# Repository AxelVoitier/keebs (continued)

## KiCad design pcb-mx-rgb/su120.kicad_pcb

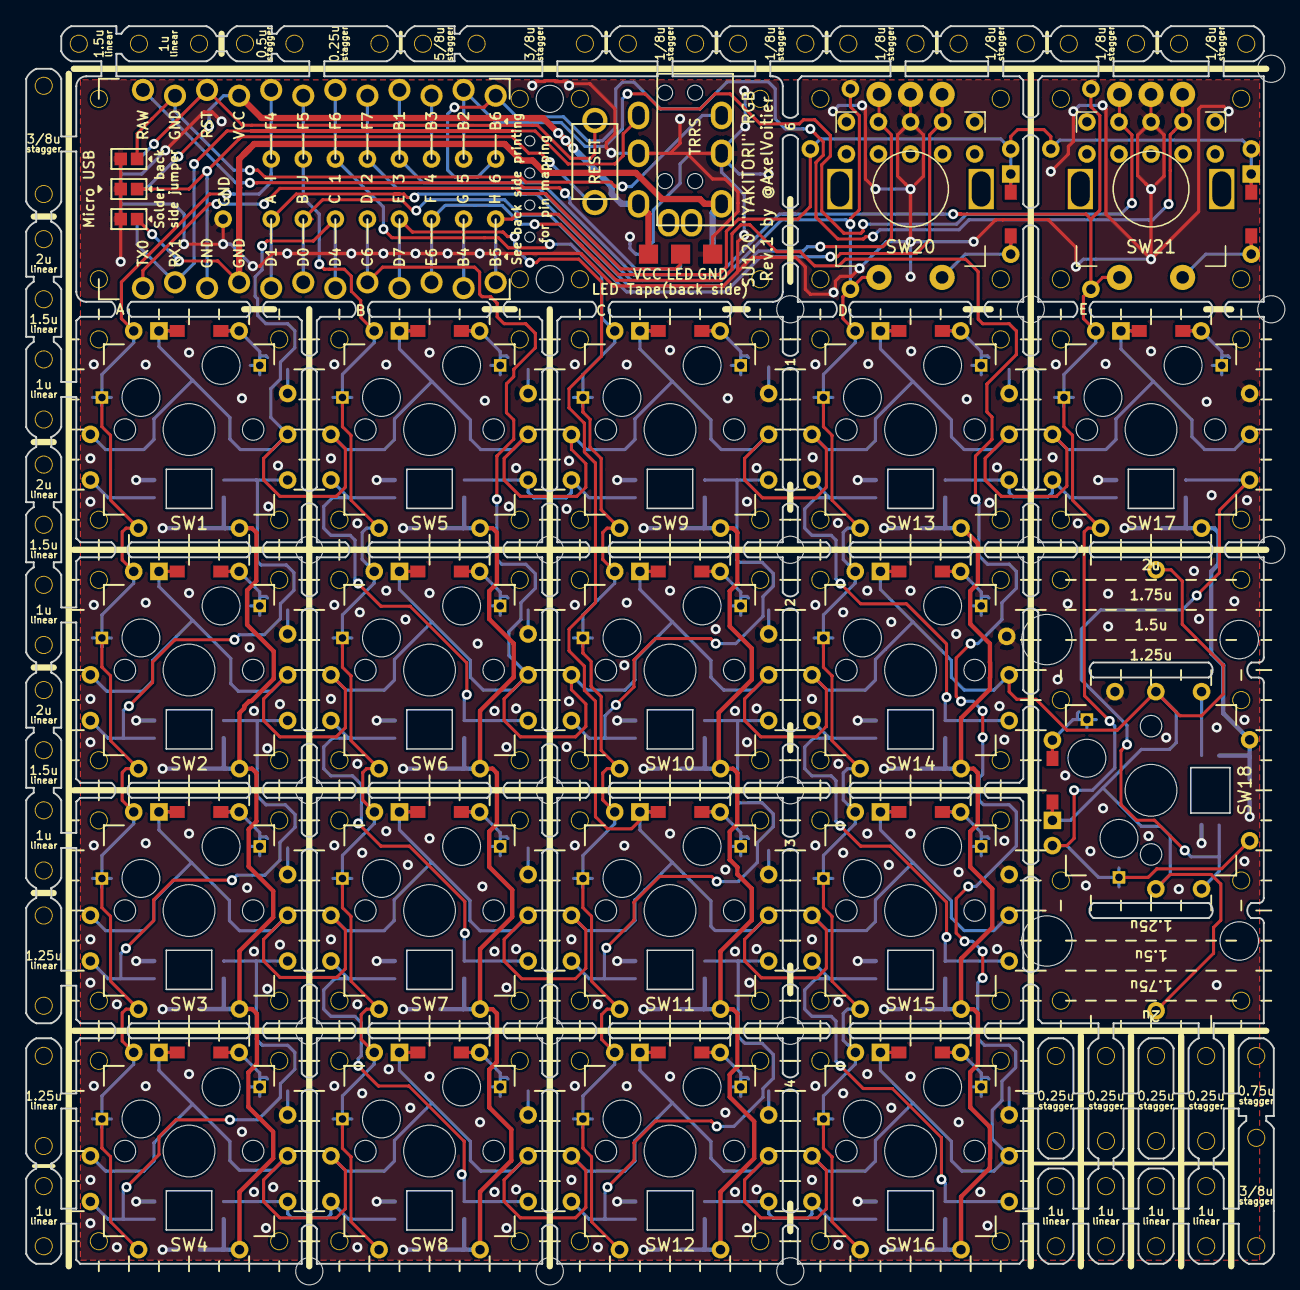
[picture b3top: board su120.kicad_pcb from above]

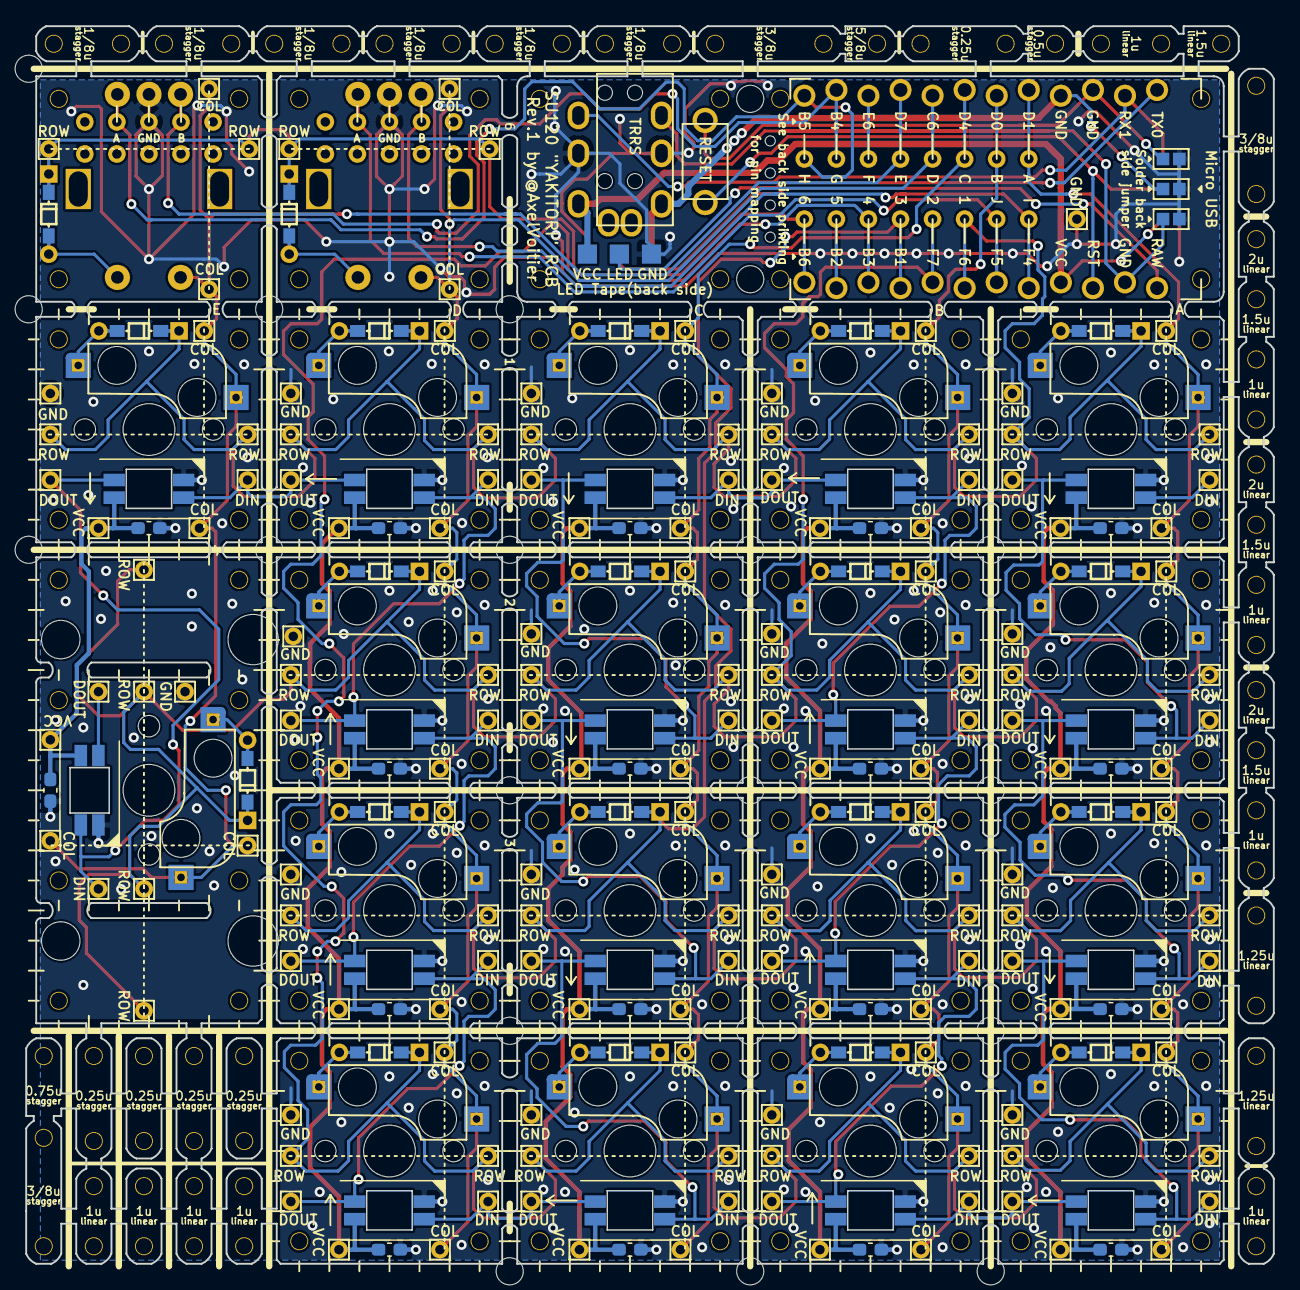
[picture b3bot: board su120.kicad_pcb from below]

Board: 2 copper layers, 98.8 x 98.0 mm, 229 parts (24 on the bottom side), 64 nets.

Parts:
C1, C2, C3, C4, C5, C6, C7, C8, C9, C10, C11, C12, C13, C14, C15, C16, C17, C18: 100n; C_0603_1608Metric_Pad1.08x0.95mm_HandSolder
D1, D2, D3, D4, D5, D6, D7, D8, D9, D10, D11, D12, D13, D14, D15, D16, D17, D18, D19, D20: D; diode_TH_SMD_rev2
H1, H2, H3, H4, H5, H6, H7, H8, H9, H10, H11, H12, H13, H14, H15, H16, H17, H18, H19, H20, H21, H22, H23, H24, H25, H26, H27, H28, H29, H30, H31, H32, H33, H34, H35, H36, H37, H38, H39, H40, H41, H42, H43, H44, H45, H46, H47, H48, H49, H50, H51, H52, H53, H54, H55, H56, H57, H58, H59, H60, H61, H62, H63, H64, H65, H66, H67, H68, H69, H70, H71, H72, H73, H74, H75, H76, H77, H78, H79, H80, H81, H82, H83, H84, H85, H86, H87, H88, H89, H90, H91, H92, H93, H94, H95, H96, H97, H98, H99, H100, H101, H102, H103, H104, H105, H106, H107, H108, H109, H110, H111, H112, H113, H114, H115, H116, H117, H118, H119, H120, H121, H122, H123, H124, H125, H126, H127, H128, H129, H130, H131, H132, H133, H134, H135, H136, H137, H138, H139, H140, H141, H142, H143, H144, H145, H146, H147, H148, H149, H150, H151, H210, H211, H212, H213: MountingHole_Pad; 1pin_conn
J1, J6: MJ-4PP-9
J2, J5: Conn_01x03; StripLED_rev2
J3, J4: Conn_01x08; PinHeader_1x08_P2.54mm_Vertical_rev2
J7, J8: Conn_02x05_Odd_Even; IDC-Header_2x05_P2.54mm_Vertical
JP1, JP2, JP3, JP4, JP5, JP6: SolderJumper_2_Open; SolderJumper-2_P1.3mm_Open_Pad1.0x1.0mm
SW1, SW2, SW3, SW4, SW5, SW6, SW7, SW8, SW9, SW10, SW11, SW12, SW13, SW14, SW15, SW16, SW17, SW18: SW_PUSH_LED; CherryMX_MidHeight_RGB_Hotswap
SW20, SW21: Rotary_Encoder_Switch; RotaryEncoder_Alps_EC11E-Switch_Vertical_H20mm_rev2
SW22: SW_Push; ResetSW
U1: ProMicro; ArduinoProMicro-ZigZag_rev5

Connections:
GND: C1.2, C2.2, C3.2, C4.2, C5.2, C6.2, C7.2, C8.2, C9.2, C10.2, C11.2, C12.2, C13.2, C14.2, C15.2, C16.2, C17.2, C18.2, H52.1, H54.1, H56.1, H57.1, H64.1, H66.1, H68.1, H70.1, H81.1, H83.1, H85.1, H92.1, H94.1, H96.1, H98.1, H109.1, H111.1, H141.1, H143.1, J1.C, J2.3, J5.3, J6.C, J7.6, J8.6, JP1.2, JP2.2, JP3.2, JP4.2, JP5.2, JP6.2, SW1.3, SW2.3, SW3.3, SW4.3, SW5.3, SW6.3, SW7.3, SW8.3, SW9.3, SW10.3, SW11.3, SW12.3, SW13.3, SW14.3, SW15.3, SW16.3, SW17.3, SW18.3, SW20.C, SW21.C
unnamed: D1.2, SW1.6
unnamed: D2.2, SW5.6
unnamed: D3.2, SW9.6
unnamed: D4.2, SW13.6
unnamed: D5.2, SW17.6
unnamed: D6.2, SW2.6
unnamed: D7.2, SW6.6
unnamed: D8.2, SW10.6
unnamed: D9.2, SW14.6
unnamed: D10.2, SW4.6
unnamed: D11.2, SW3.6
unnamed: D12.2, SW7.6
unnamed: D13.2, SW11.6
unnamed: D14.2, SW15.6
unnamed: D15.2, SW8.6
unnamed: D16.2, SW18.6
unnamed: D17.2, SW16.6
unnamed: D18.2, SW20.S2
unnamed: D19.2, SW21.S2
unnamed: D20.2, SW12.6
unnamed: H51.1, SW1.4
unnamed: H53.1, H59.1, SW1.2, SW2.4
unnamed: H55.1, H61.1, SW2.2, SW3.4
unnamed: H65.1, H74.1, SW5.4, SW6.2
unnamed: H67.1, H76.1, SW6.4, SW7.2
unnamed: H72.1, H80.1, SW5.2, SW9.4
unnamed: H78.1, SW18.2
unnamed: H82.1, H87.1, SW9.2, SW10.4
unnamed: H84.1, H89.1, SW10.2, SW11.4
unnamed: H100.1, H108.1, SW13.2, SW17.4
unnamed: H93.1, H102.1, SW13.4, SW14.2
unnamed: H95.1, H104.1, SW14.4, SW15.2
unnamed: H97.1, H106.1, SW15.4, SW16.2
unnamed: H63.1, H110.1, SW3.2, SW4.4
unnamed: H112.1, H147.1, SW4.2, SW8.4
unnamed: H91.1, H142.1, SW11.2, SW12.4
unnamed: H71.1, H145.1, SW17.2, SW18.4
unnamed: H69.1, H149.1, SW7.4, SW8.2
unnamed: H99.1, H151.1, SW12.2, SW16.4
VCC: C1.1, C2.1, C3.1, C4.1, C5.1, C6.1, C7.1, C8.1, C9.1, C10.1, C11.1, C12.1, C13.1, C14.1, C15.1, C16.1, C17.1, C18.1, H58.1, H60.1, H62.1, H73.1, H75.1, H77.1, H79.1, H86.1, H88.1, H90.1, H101.1, H103.1, H105.1, H107.1, H144.1, H146.1, H148.1, H150.1, J1.D, J2.1, JP6.1, SW1.1, SW2.1, SW3.1, SW4.1, SW5.1, SW6.1, SW7.1, SW8.1, SW9.1, SW10.1, SW11.1, SW12.1, SW13.1, SW14.1, SW15.1, SW16.1, SW17.1, SW18.1, U1.21
X1: H1.1, H6.1, H21.1, H25.1, H26.1, H30.1, H113.1, H118.1, J4.1, SW1.5, SW2.5, SW3.5, SW4.5, U1.5
X2: H2.1, H7.1, H22.1, H27.1, H114.1, H117.1, H119.1, H122.1, J4.2, SW5.5, SW6.5, SW7.5, SW8.5, U1.6
X3: H3.1, H8.1, H23.1, H28.1, H115.1, H120.1, H210.1, H211.1, J4.3, SW9.5, SW10.5, SW11.5, SW12.5, U1.7
X4: H4.1, H9.1, H24.1, H29.1, H42.1, H44.1, H116.1, H121.1, H133.1, H135.1, J4.4, SW13.5, SW14.5, SW15.5, SW16.5, SW20.S1, U1.8
X5: H5.1, H10.1, H41.1, H43.1, H134.1, H136.1, J4.5, SW17.5, SW18.5, SW21.S1, U1.9
X6: J4.6, U1.10
X7: J4.7, J8.4, SW21.B, U1.11
X8: J4.8, J8.8, SW21.A, U1.12
X9: J3.1, J7.4, SW20.B, U1.20
X10: J3.2, J7.8, SW20.A, U1.19
Y1: D1.1, D2.1, D3.1, D4.1, D5.1, H11.1, H12.1, H13.1, H14.1, H15.1, H16.1, H17.1, H18.1, H19.1, H20.1, J3.3, U1.18
Y2: D6.1, D7.1, D8.1, D9.1, D16.1, H31.1, H32.1, H33.1, H34.1, H35.1, H36.1, H37.1, H38.1, H45.1, H46.1, H49.1, H50.1, J3.4, U1.17
Y3: D11.1, D12.1, D13.1, D14.1, H123.1, H124.1, H125.1, H126.1, H127.1, H128.1, H129.1, H130.1, J3.5, U1.16
Y4: D10.1, D15.1, D17.1, D20.1, H39.1, H40.1, H47.1, H48.1, H131.1, H132.1, H212.1, H213.1, J3.6, U1.15
Y5: J3.7, U1.14
Y6: D18.1, D19.1, H137.1, H138.1, H139.1, H140.1, J3.8, U1.13
data: J1.B, JP1.1, U1.2
dummyVCC: J5.1, J6.D, JP5.1, U1.4
dummydata: J6.B, JP2.1, U1.23
dummyled: J5.2, U1.24
led: J2.2, U1.1
reset1: JP4.1, SW22.1, U1.22
reset2: JP3.1, SW22.2, U1.3

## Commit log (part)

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2021-10-07 Work In Progress
    - Duplicated original su120
    - Forked the switch footprint to remove choc socket and add RGB chip
    - Started converting columns 1 and 2 to the new footprint
    - Started cleaning the schematic for these columns
    - Added solder points for relaying DIN, DOUT, VCC and GND for the RGB chips in between boards
    - Attempt at new routing strategy in column 1 row 2
2021-10-11 Adding initial top plate for Kyfle.
    Kyfle is a mix of Kyria layout with an extra row, using some Sofle design files, and using a modified (for RGB) su120 bit boards as actual PCB
2021-10-12 Importing PCB design from SU120 branch (was already modified to fit RGB on the branch)
2021-10-12 Working on solutions to hold the main PCB.
    Also cleaned a bit the layers by separating physical dimensions (CrtYrd), functional wiring (Fab) and other construction lines (User).
    Completed the wiring template.
2021-10-15 Settled on a solution to fix the PCB
    It will be hold by the bottom plate only.
2021-10-15 Fixuturing solution for the pro micro board
2021-10-18 Adding 3D model for cherry mx (from Acheron libs), adding generating pretty pictures with it
2021-10-21 Redid some footprints
    - For the pro-micro socketed with rivets, it is now reversible
    - The connector for OLED screen has also been converted to a rivetted version
    - The footprint of the TRRS connector has been corrected according to part datasheet
    - The silkscreen indicating the cut line in between bit boards is now done in some slots footprints
2021-10-25 Massive redesign
    - Realised the design was not reversible. Only solution was to mirror the two diagonal holes of each bit. But one of them was coliding with hotswap socket footprint. Until...
    - I also realised that having the holes at these Y positions made the screw coming on top collide with the bottom of the switch housing...
    - So switched to having two holes right in between each bit (vertically).
    - Then I realised cheap pcb houses can have quite some limitations when it comes to exotic uses of slots. In particular, for jlcpcb:
    * They prefer tabs to be >= 4mm wide
    * They prefer at least 3mm of PCB next to a slot (ie. avoid slim inter-slots parts)
2021-10-28 Plates outlines finished
    Redefined the various outlines of the plates based on the new constrains.
    For the top dimension, I took the largest middle-finger stagerring I could find (Elephant42, at +9.5mm) and rounded it to 10mm max amplitude in the middle finger rail, and used that as reference for 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
    And defined the position of the rest from that.
    Top left M% hole might need to be reviewed.
2021-10-30 Resized M2 slots and holes to 2mm instead of 2.2mm
    After receiving M2 hardware, I noticed 2mm opening would provide a tighter and less wobbly fit than the typical M2 clearance of 2.2mm.
    Also, finished the silkscreen of bottom plate, as well as M2 holes for encoders in top plate.
    At this point, both top and bottom plate could be considered finished.
2021-11-01 It is never done. Adding plethora of plate variants.
    - Variant of the default top plate with less routing involved
    - Variant of a top plate allowing to slide the switches around
    - Variant of that last top plate with less routing involved
    Also moving few minor things here and there.
2021-11-03 Plates: Received M2 and M5 hardware. It's bigger than specified...
    - M5 screw head is ~9.5 instead of 8.7. Was colliding in the top left
    corner with M2 screw for pro micro board. So I shifted up pro micro
    board 0.3mm.
    - M2 screw head is also larger than expected (3.8 instead of 3.2). But
    it is mostly fine as I was designing with 4-4.2mm clearance. Only
    exception was for screws supporting the middle bottom section of top
2021-11-03 Adding footprint for 5-way switch (panasonic and also compatible Alexpress noname one)
    Not used on PCB yet as I haven't found a suitable position
2021-11-04 Tentative routing of the 5-way switch
    Not yet integrated in the main board itself.
2021-11-06 PCB: Adding mouse bites to break away tabs
    And increasing tabs width from 4mm to 5mm.
2021-11-08 Adding Pimonori trackball footprint (for reference)
2021-11-08 Adds mouse bites to top plate with rails
2021-11-11 Massive reorganisation, renaming, and licensing
    Kyfle is now called Lergo
2021-11-11 Pimoroni spelling is hard :D
2021-11-13 Integrating Pimoroni trackball in all top plates.
2021-11-15 Lergo V1.A, ready for first prototype run
2021-11-15 Remove outdated images
2021-11-17 Following modifications for aluminum PCBs, FR4 and Alu variants are now available
2021-11-17 Adding illustrations
2021-11-29 Create basic README.md for now
2023-09-27 Handy: Adding KLE generated output, and first throw at layout
    Layout is a WIP, as it is just imported from my current Lergo setup, but not fully adapted yet.
2023-09-28 Handy: Adapt left nav cluster to use Page up/down, home/end
2023-09-29 Handy: Splitting ergogen config file into few smaller and less confusing files, thanks to a new merge helper tool in keebs.py
2023-09-30 Handy: Many changes to the keymap. Also enhanced the config "language" for it.
2023-10-01 Scripts: Supports setting a custom name in KLE output
2023-10-01 Scripts: Integrate ergogen as a Docker container
    Streamlines the workflow as the generation of points.yaml and units.yaml is no longer manual.
    Ie. using the Makefile, you can now go from just the ergogen config overlays up to the final results (currently mostly KLE output) in one command.
2023-10-03 Bunch of enhancements
    - Now generated coordinates are automatically aligned to top-left corner, with positive Y going down (inverse of ergogen), as this fits most tools. KLE or QMK offsets are no longer needed.
    - Keymap entries are now called legend instead of value.
    - In QMK info.json generation, we now support deleting pre-exsiting entries (that's to purge old fields, or some bogus ones from qmk new-keyboard template).
    - QMK keymap.json generation completed with support for tranparent keycodes, and on-hold layer change (ie. "LT"). It is smart enought to take care of all the little details around using LT correctly.
    AND vvvvvv
    - We can auto generate layout in .c/.h files!!!!!!
2023-10-08 Firmware compilation imporvements
    - Deal with the new way of QMK handling keyboard, keymap and userland.
    - Allows to set configs in keymap.json.
    - Separate info.json from keymap.json generation.
    - When generating info.json, if the keyboard folder does not exist, we use "qmk import-keybord" with the json file to create the keyboard.
    - Add support for various quantum keycodes (bootloader reset, dymanic tapping term, auto shift).
2023-12-30 Adding option to KLE generation to ignore a key or layer
2023-12-31 Handy: Updating readme and images
2024-01-05 Handy: Starting to streamline KiCad generated parts
    Here is implemented the PCB outline footprint generation.
    As a side effect, we also ensure that fp-lib-table KiCad project file includes an Ergogen.pretty footprint library.
2024-01-05 KiCad: Supporting footprints in PCB
2024-01-05 KiCad: Easier API to parse/export
2024-01-06 Kicad, footprints: Supports fp_circle, fp_poly, pad, and model token
    Test with a fairly complex footprint.
    Lotssss of underlaying modifications to make it work.
2024-01-06 Kicad: Significant reduction in verbosity when declaring fields
2024-01-08 Handy: Do not outline mirrored keys
2024-01-14 Handy: Proper case implementation
    Since there is now "preprocessin" capabilities added to ergogen by keebs.py script, it can now calculate precisely some of the difficult points (usually corners) that are defined by intersection and/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
    Tenting holes have been added as well, with an option for the "inner" top tenting screw being either near the middle (to be parallel to the right edge) or all the way to the left (vertically aligned 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
    Also cleaned up a bit all the outlines, added premises of components, starting with promicro, oled screen and te
2024-01-14 Handy: Minor fixes here and there
2024-01-15 KiCad, tests: Fixes tests not passing because of kicad inconsistencies
2024-01-15 Kicad: Fixes for footprint having desr and tags
2024-01-15 Handy: Finally generating a proper outline
2024-01-28 KiCad: Implementing a current parsing context stack
    It can be used by token classes to "specify" some of their behaviour during parsing.
    It should finally be the foundation of a fix for the various KiCad tokens that have the same name but not the same format... (eg. layer).
2024-01-28 KiCad: Adding more flexible newlines control
2024-01-31 Kicad: Nails further issues with angles...
    Despite the special casing done in _angle_normalizer for fp_text and pad, there was still some unnecessary modifications of, eg. 355 to -5.
    This was due to the way footprint are updated: for every item in the model footprint (which usually is built with a 0 degree reference), a new item with angle applied (the one of each particular ref 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
    Issue was that this new item used for comparison to the old one was ha
2024-01-31 KiCad: Fixes bug introduced by one speed optimisation
    In case of loading different kicad_pcb files of different versions within the same instance of a script, some versioned token of the wrong version were weirdly used. But if parsing each file independ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
    Turns out, the method doing the resolution of versioned token was cached in such a way that if later it was used in the context of a different version, then it was using the cached result from the fi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
    Taking the version context out of that method, and instead passing the current version as an argument to it fixes the issue.
2024-02-04 Kicad: Reorganise token classes declarations such that we can use attrs.resolve_types directly in Token.__init_subclass__.
2024-02-24 Linting issues
2026-01-22 Framework, OKM: Adding images
2026-01-22 FW OKM: Reduce aperture to 16.6 mm (was 16.75)
2026-01-24 FW: First throw at Handywork-min layout, a 5x3 adapted to a Framework 16
2026-01-24 HandyWork: Big update with 3 main layouts and 4 more variants
2026-01-25 HandyWork: Keymap and documentation for all 8 proposed layouts
2026-01-25 HandyWork: Adding description of the main properties
2026-02-16 Update on the Framework footprints
2026-02-23 Framework, A1 board footprint: Correction of bottom courtyard
2026-03-01 Framework, One Key Module footprints: various changes
    - Added "OKM" keyword/tag.
    - Reduced bottom courtyard from 19.2mm to 18mm square. This avoid DRC errors when placing keys next to each other.
    - Made the tab slots pins duplicates of pin 2 and 10 (GND).
    - Pulled back the SMD pads by 0.1mm from edge to respect a typical 0.2mm margin from edge from PCB fab houses.
2026-03-01 Framework: Updating OKM CAD model image with the 0.2mm pullback from edge
2026-03-01 HandyWork: Adding fully routed PCB for 5x3 + Mods + Nav
2026-03-02 HandyWork 5x3 + Mods + Nav: Silkscreen update
    Adds delimiters to help placement of foam
2026-03-03 HandyWork: Refactor vias to not use 0.2mm drill in order to be significantly cheaper (~50% for the PCB itself)
2026-03-04 HandyWork: Adding placeholder for production QR code / serial number
2026-03-04 HandyWork 5x3-M-N: Fixing the schematic that got broken by raw copying it from the template
2026-03-04 HandyWork: Adding aluminum plate
2026-03-04 HandyWork 5x3-M-N: Rename properly the AluPlate project
2026-03-06 Framework footprint: Switching license to CERN OHL-P
2026-03-06 HandyWork 5x3-M-N: Update of README
2026-03-10 HandyWork 5x3-M-N: Generating a firmware that compiles
